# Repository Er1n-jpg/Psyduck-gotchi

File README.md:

# PsyduckGotchi (Tamagotchi Project)

Psyduck-gotchi (gotchu!) is a my very first project I ever made for fallout. I made this using the tamagotchi tutorial on the fallout site!
A tamagotchi is basically a virtual pet you can take care of with stats indicating it's happiness, energy and hunger. It's a silly little thing that you can bring around and make you feel like you're taking care of something, Psyduck runs off an ESP32 with LIPO battery compatibility

# How this works!
My tamagotchi project has 3 buttons, an LCD screen, a buzzer, and has neopixels for the LED backlighting. 
When you first boot up the OLED display, it should contain the Energy, Happiness and Hunger stats on the screen. 

3 different screens will be played on the OLED. If psyduck looks happy, it means that one of your stats (happiness, energy, hunger) is above 60. If psyduck is neutral than your stats are between 60 and 30 (should be fine, leave him alone for a bit!). If psyduck is sad then all of your stats are below 30%. His stats will decrease overtime like a real pet.
Careful! Psyduck can die ... :(. If all of your stats are under 5% then psyduck will die!! Don't worry though, he's not dead forever, just for a minute, after that his stats return to normal again!

the 3 buttons on the tamagotchi do as follows:
Left button: Feed the duck
              - When you press the button, the virtual pet will be fed! Used when hunger bar is low 
Middle button: Play with the duck
              - When you press the middle button, the you can play with the virtual pet! This is used when the happiness bar is low
Right button: Put the duck to sleep
              - When you press the middle button, you will put the duck to sleep, a sleeping image is played! This is used when the energy is low

Everytime a button is clicked, the buzzer will play a sound.

# why I made this

I made this project since I thought it would be a super good first hardware project instead of making hackpads like everyone else. I also made this since I thought 
it would be a challenge for me to CAD since I had previous CAD experience. This is also a birthday present for a friend who looooves psyduck ( a very very cute and stupid pokemon). It's stereotypical that
I try to buy something psyduck themed but I thought since I had the 3D printer filament, why not go for a psyduck printed item (oops I hope I have enough filament).

# CAD model
Here's the ONshape assembly of my project

you can also check it out [here](https://cad.onshape.com/documents/41e01f73df5ff1d754294f2c/w/e586c19b9efa3d71e410a140/e/51dadf3c9c8fd63de1790a83)

# PCB
Here's the wiring schematic and traces of my PCB as well as a kicad's 3D render

Schematic ^^

Traces^^

3D render^^

# BOM (bill of materials)
[Tamagotchi BOM - Sheet1.csv](https://github.com/user-attachments/files/29111727/Tamagotchi.BOM.-.Sheet1.csv)

| Item | Description | Quantity (#) | Unit Price ($) | Shipping ($) | Total Price ($) |
| --- | --- | --- | --- | --- | --- |
| PCB | PCB quote from JLCPCB | 1 | $2.00 | $2.50 | $4.50 |
| ESP32 | Seed Studio XIAO ESP32 | 1 | $4.94 | $18.31 | $23.25 |
| OLED | 128 x 64 OLED LCD | 1 | $4.00 | --- | $4.00 |
| Buzzer | Passive Buzzer | --- | 5 | $0.06 | $0.50 |
| Buttons | Hropart round buttons| --- | 5| $0.11 | $0.50 |
| LED | Yongyutai LED's | 50 | $0.01 | $0.50 |
| LCSC shipping | --- | --- | --- | --- | $14.51 |
| Total | --- | --- | --- | 35.32 | $45.32 |

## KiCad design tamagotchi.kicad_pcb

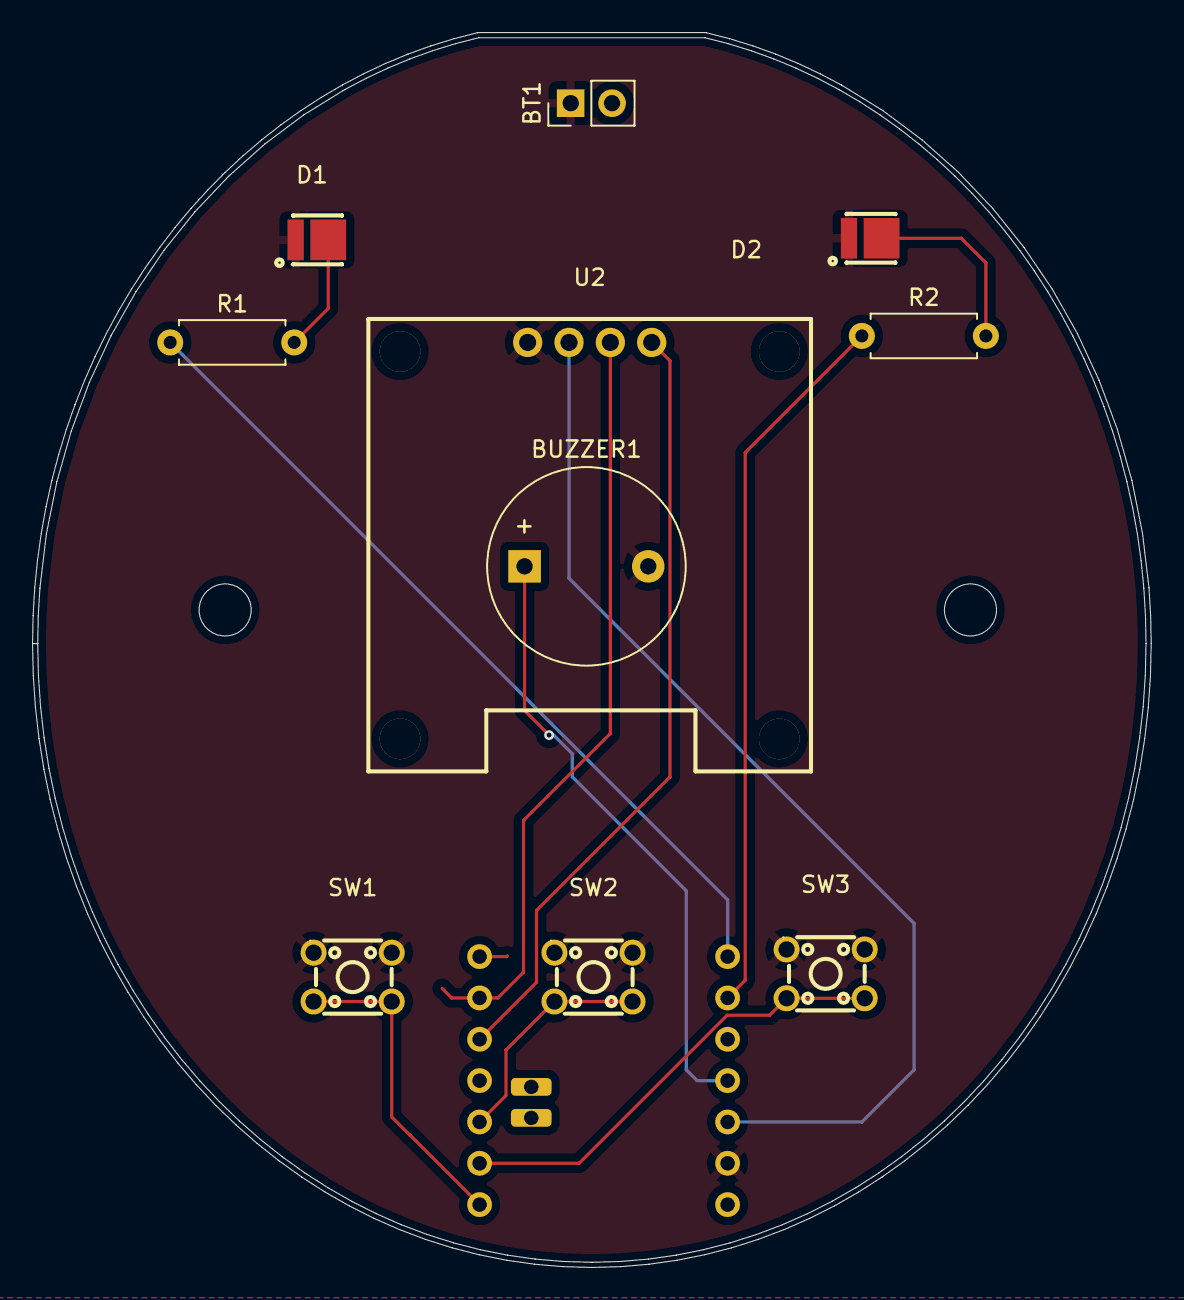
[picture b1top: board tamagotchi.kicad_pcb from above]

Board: 2 copper layers, 68.7 x 75.8 mm, 11 parts (1 on the bottom side), 12 nets.

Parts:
BT1: Battery_Cell; PinHeader_1x02_P2.54mm_Vertical
BUZZER1: 1207-P6.5MM; Buzzer_12x9.5RM7.6
D1, D2: LED; LED-SMD_L3.0-W3.0_WHITE
R1, R2: R220; R_Axial_DIN0207_L6.3mm_D2.5mm_P7.62mm_Horizontal
SW1, SW2, SW3: SW_Push; SW-TH_4P-L4.5-W4.5-P3.00-LS4.8
U1: XIAO-ESP32-C3-SMD; XIAO-ESP32-C3-DIP-SMD
U2: HS96L03W2C03; OLED-TH_L27.8-W27.2-P2.54_C9900033791

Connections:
+3V3: U1.12 (3V3), U2.2 (VCC)
GND: BT1.1 (+), BUZZER1.2 (-), D1.1 (K), D2.1 (K), SW1.1, SW2.1, SW3.1, U1.13 (GND), U2.1 (GND)
unnamed: BUZZER1.1 (+), U1.11 (GPIO10_D10_MOSI)
unnamed: D1.2 (A), R1.2
unnamed: D2.2 (A), R2.2
unnamed: SW1.2, U1.1 (GPIO2_A0_D0)
unnamed: SW3.2, U1.2 (GPIO3_A1_D1)
unnamed: SW2.2, U1.3 (GPIO4_A2_D2)
unnamed: U1.5 (GPIO6_D4_SDA), U2.4 (SDA)
unnamed: U1.6 (GPIO7_D5_SCL), U2.3 (SCL)
unnamed: R2.1, U1.9 (GPIO8_D8_SCK)
unnamed: R1.1, U1.8 (GPIO20_D7_RX)

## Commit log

2026-06-13 first commit lets see how the change
2026-06-13 Add temporary image to README
2026-06-16 Update README with Psyduck-gotchi project details
    Added detailed project description and features of the Psyduck-gotchi virtual pet project.
2026-06-16 Add 3D render section to README
    Added a 3D render image section to the README.
2026-06-16 Update README with project details and images
    Added images and details about the tamagotchi project, including button functions and CAD experience.
2026-06-16 Enhance README with button descriptions and images
    Added descriptions for button functionalities and updated images.
2026-06-16 yay uploady uploayd
2026-06-18 Delete Fallout zine (2).png
    updating zine
2026-06-18 change da colourrrr
2026-06-18 Update README with project details for PsyduckGotchi
    Added project description and features for PsyduckGotchi.
2026-06-18 Fix heading formatting in README.md
    please work
2026-06-18 Enhance README with additional project details
    Expanded description of the tamagotchi project to include details about the hardware and functionality.
2026-06-18 Clarify tamagotchi project features in README
    Updated the README to clarify project features and functionality.
2026-06-18 Revise README for clarity and additional details
    Updated the README to clarify button functions and project motivation.
2026-06-18 adding BOM
    Added a bill of materials section with item details and pricing.
2026-06-18 please work
2026-06-18 Add table to README for better data presentation
2026-06-18 Fix table formatting and update item prices in README
    Updated item table formatting and corrected values.
2026-06-18 Fix formatting issue in OLED entry in README
2026-06-18 Fix BOM table formatting in README
    Updated BOM table formatting for clarity.
2026-06-18 Update parts list with Buzzer, Buttons, and LED
    Added new components to the parts list in the README.
2026-06-18 Update README with image and formatting changes
    Added an image to the README and made minor formatting adjustments.
2026-06-18 Update README with Psyduck stats behavior
    Added information about Psyduck's stats decreasing over time and the consequences of low stats.
2026-06-18 Add CAD model section to README
    Added a section about the CAD model and included an image link.
2026-06-18 Add files via upload
    CAD files
2026-06-18 5000th readme edit
2026-06-24 Rename tamagotchi.ino.ino to tamagotchi.ino
